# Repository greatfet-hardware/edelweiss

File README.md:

# Edelweiss
A GreatFET Neighbor for the TI CC1310 sub-GHz radio IC.

Required KiCad dependency:

https://github.com/greatscottgadgets/gsg-kicad-lib

If you are using git, the preferred way to install gsg-kicad-lib is to use the
submodule:

```
git submodule init && git submodule update
```

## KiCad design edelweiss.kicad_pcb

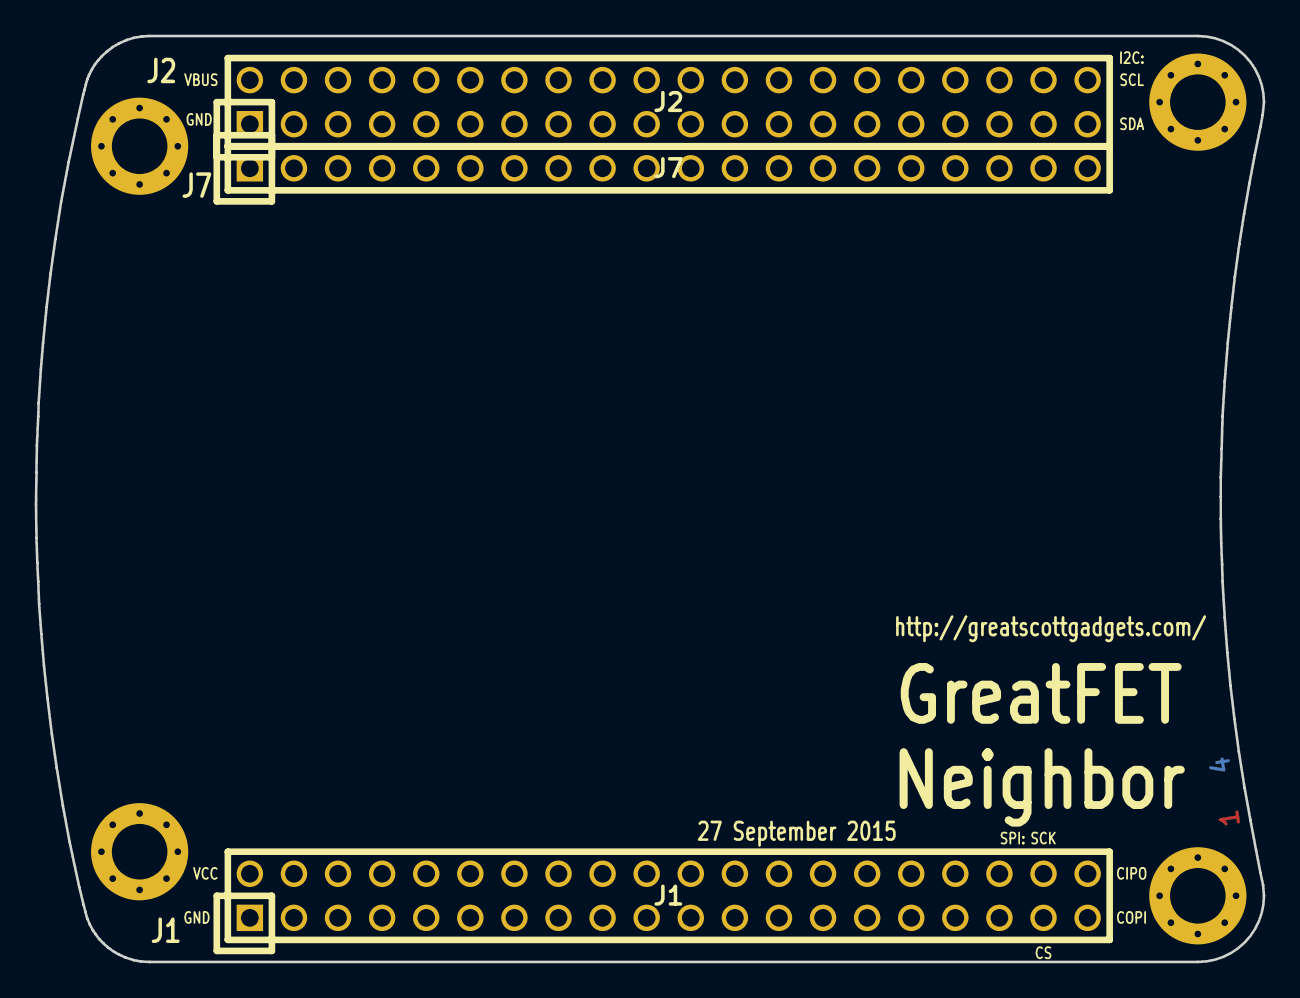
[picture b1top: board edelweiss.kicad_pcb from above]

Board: 4 copper layers, 70.7 x 53.3 mm, 7 parts (0 on the bottom side), 2 nets, no tracks yet.

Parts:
J1: NEIGHBOR1; HEADER-2x20
J2: NEIGHBOR2; HEADER-2x20
J7: BONUS_ROW; HEADER-1x20
MH1, MH2, MH3, MH4: MOUNTING_HOLE; HOLE126MIL-COPPER

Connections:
GND: J1.1, J2.1, J7.1, J7.10, J7.19, MH1.1, MH2.1, MH3.1, MH4.1
VCC: J1.2, J7.20

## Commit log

2019-05-27 split edelweiss into separate repository
2020-07-03 adopt OSHWA convention for SPI signal names https://www.oshwa.org/a-resolution-to-redefine-spi-signal-names
